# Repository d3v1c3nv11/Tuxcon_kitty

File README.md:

# DIY: Tuxcon_kitty

Olimex's Tuxcon kitty

Arduino sketch file: https://github.com/d3v1c3nv11/Tuxcon_kitty/tree/master/hello_kitty

Hardware: https://github.com/d3v1c3nv11/Tuxcon_kitty/tree/master/Tuxcon_Kitty_hardware

Schematic in pdf format: https://github.com/d3v1c3nv11/Tuxcon_kitty/blob/master/tuxcon_kitty.pdf

################## IMPORTANT NOTE ##################

 Tuxcon Kitty board is preprogramed with modified micronucleus-t85 bootloader. You can download from here: https://github.com/d3v1c3nv11/micronucleus-t85

################## ENJOY! ##################

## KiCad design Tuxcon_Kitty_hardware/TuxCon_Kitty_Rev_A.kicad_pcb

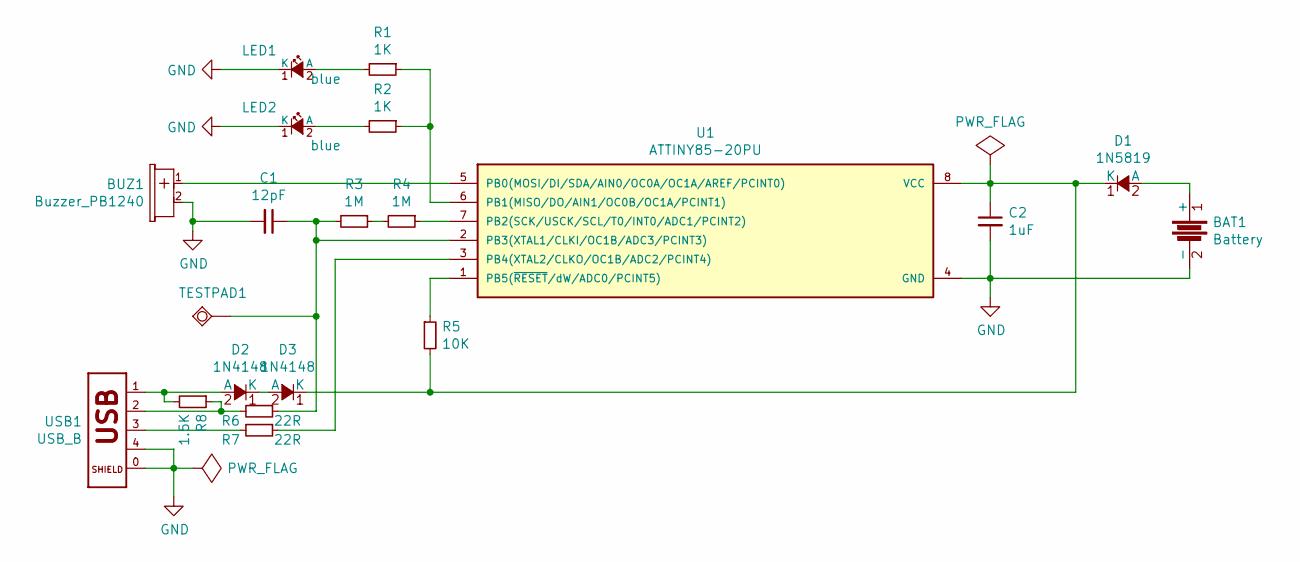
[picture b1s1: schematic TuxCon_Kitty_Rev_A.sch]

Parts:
BAT1: Battery; CR2032H_PTH
BUZ1: Buzzer_PB1240; BUZZER-PB1240
C1: 12pF; C_1206_5MIL_DWS
C2: 1uF; C_1206_5MIL_DWS
D1: 1N5819; SOD80C-4148-KA
D2, D3: 1N4148; SOD80C-4148-KA
LED1, LED2: blue; LED-3mm-PTH-KA
R1, R2: 1K; R_1206_5MIL_DWS
R3, R4: 1M; R_1206_5MIL_DWS
R5: 10K; R_1206_5MIL_DWS
R6, R7: 22R; R_1206_5MIL_DWS
R8: 1.5K; R_1206_5MIL_DWS
TESTPAD1: TESTPAD; TP_SMD_10.00x8.00mm
U1: ATTINY85-20PU; SOIC-8
USB1: USB_B; USB_Mini-B

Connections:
GND: BAT1.2 (-), BUZ1.2 (MINUS), C1.2, C2.2, LED1.1 (K), LED2.1 (K), U1.4 (GND), USB1.0 (5), USB1.4
unnamed: BAT1.1 (+), D1.2 (A)
unnamed: BUZ1.1 (PLUS), U1.5 (PB0(MOSI/DI/SDA/AIN0/OC0A/OC1A/AREF/PCI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)
unnamed: C1.1, R3.2, R6.1, TESTPAD1.1, U1.2 (PB3(XTAL1/CLKI/OC1B/ADC3/PCINT3))
unnamed: C2.1, D1.1 (K), D3.1 (K), R5.2, U1.8 (VCC)
unnamed: D2.1 (K), D3.2 (A)
unnamed: D2.2 (A), R8.2, USB1.1
unnamed: LED1.2 (A), R1.2
unnamed: LED2.2 (A), R2.2
unnamed: R1.1, R2.1, U1.6 (PB1(MISO/DO/AIN1/OC0B/OC1A/PCINT1))
unnamed: R3.1, R4.2
unnamed: R4.1, U1.7 (PB2(SCK/USCK/SCL/T0/INT0/ADC1/PCINT2))
unnamed: R5.1, U1.1 (PB5(~RESET~/dW/ADC0/PCINT5))
unnamed: R6.2, R8.1, USB1.2
unnamed: R7.1, U1.3 (PB4(XTAL2/CLKO/OC1B/ADC2/PCINT4))
unnamed: R7.2, USB1.3

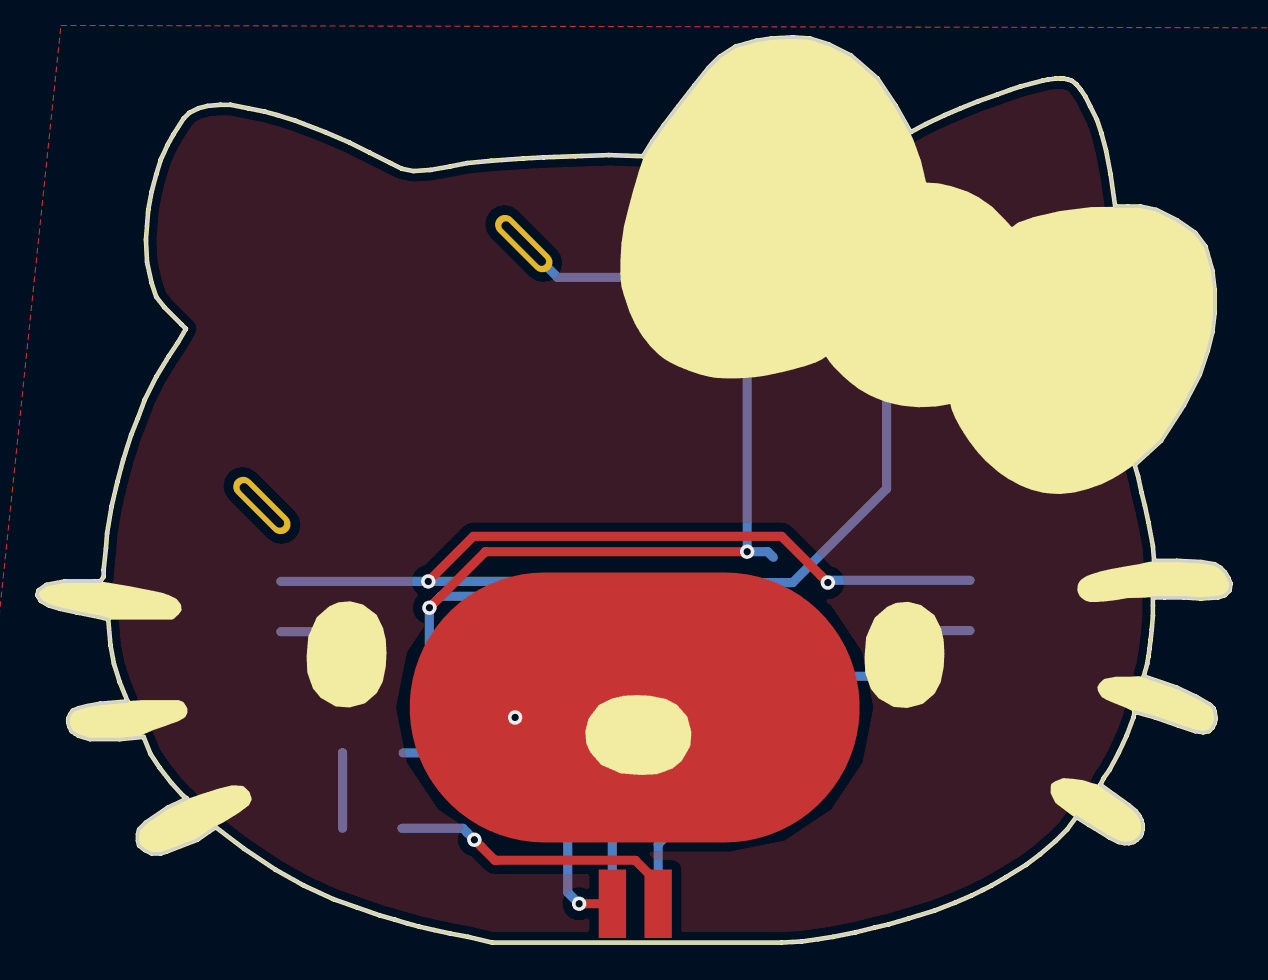
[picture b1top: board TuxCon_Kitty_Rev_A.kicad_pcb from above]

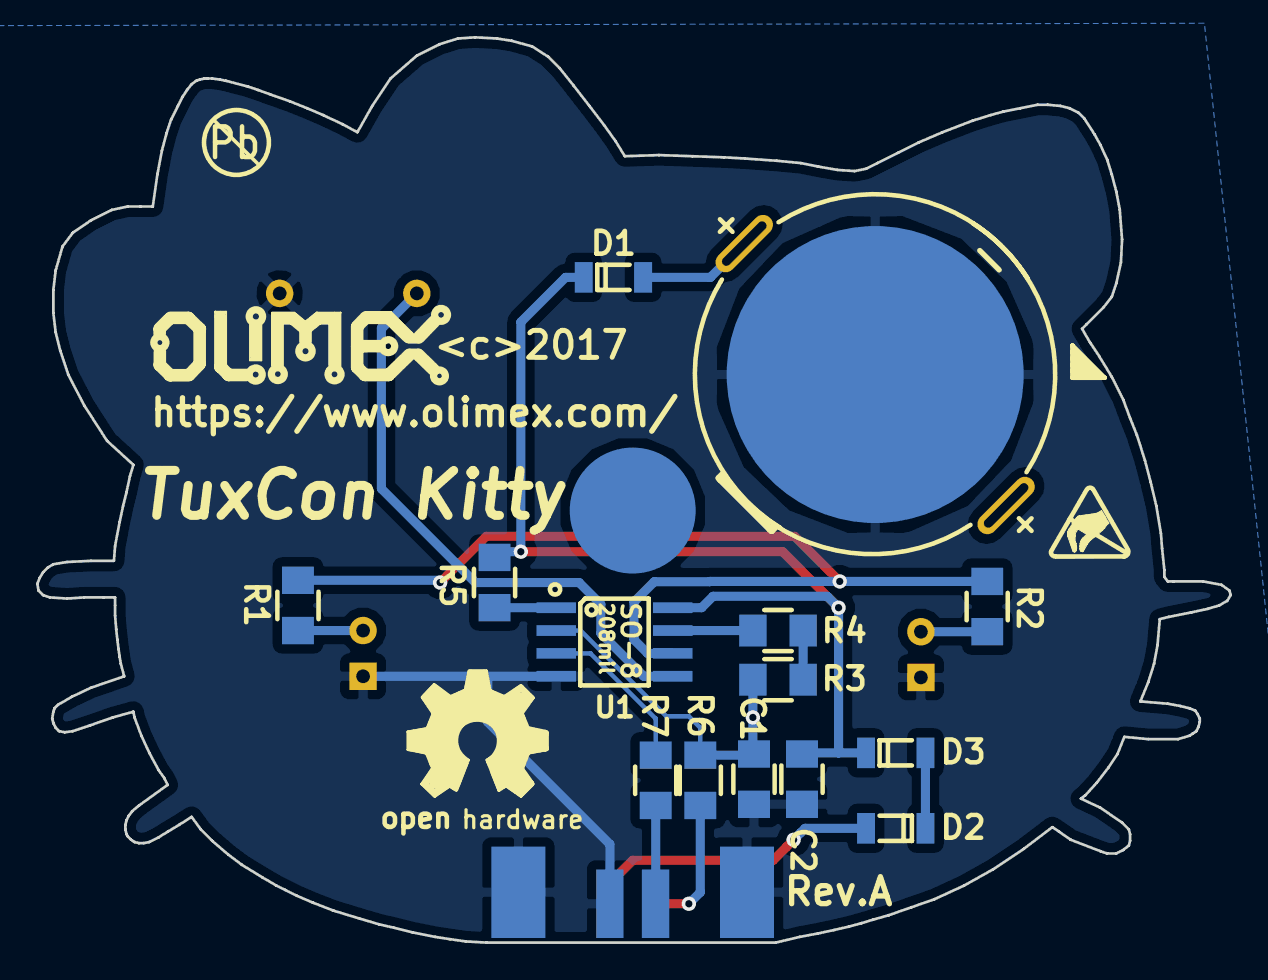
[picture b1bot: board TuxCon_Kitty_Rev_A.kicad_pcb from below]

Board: 2 copper layers, 66.3 x 50.3 mm, 21 parts (16 on the bottom side), 16 nets.

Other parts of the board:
Ref**: Val**; LOGO_ANTISTATIC_SMALL_4.5mmX2.8mm
TESTPAD1#2: TESTPAD; TP_SMD_10.00x8.00mm

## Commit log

2017-05-18 initial
2017-05-18 Schematic in pdf
2017-05-18 added link to bootloader
2017-05-18 added pic
2017-05-18 links updated
2017-05-18 added DIY :)
